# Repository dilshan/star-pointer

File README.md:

# StarPointer - Electronic Finderscope

StarPointer is a virtual electronic finderscope for astronomical telescopes. This device works with [*Stellarium*](http://stellarium.org) and helps the observer identify objects in the sky.

This sensor kit builds around the STM32F103C8 microcontroller, ADXL345 3-axis accelerometer, and HMC5883L 3-axis magnetometer. It communicates with the PC using the inbuilt USB peripheral of the STM32F103C8 microcontroller.

StarPointer is an open-source project. This repository has all the schematics, PCB design files, firmware source codes, and application source codes.

The complete documentation of this project is in the [wiki section](https://github.com/dilshan/star-pointer/wiki) of this repository. The PCB Gerber files and compiled binaries are also available in the [release section](https://github.com/dilshan/star-pointer/releases) of this repository. The PCB of the StarPointer can also [order from the *PCBWay* website](https://www.pcbway.com/project/shareproject/StarPointer_virtual_electronic_finderscope_2c7c17a4.html).

All the content of this project is distributed under the terms of the following license:

-   Hardware License: [CERN-OHL-W 2.0](https://ohwr.org/cern_ohl_w_v2.txt)
-   Software License: [MIT](https://github.com/dilshan/star-pointer/blob/main/LICENSE)
-   [Documentation](https://github.com/dilshan/star-pointer/wiki) License: [CC BY 4.0](https://creativecommons.org/licenses/by/4.0/)

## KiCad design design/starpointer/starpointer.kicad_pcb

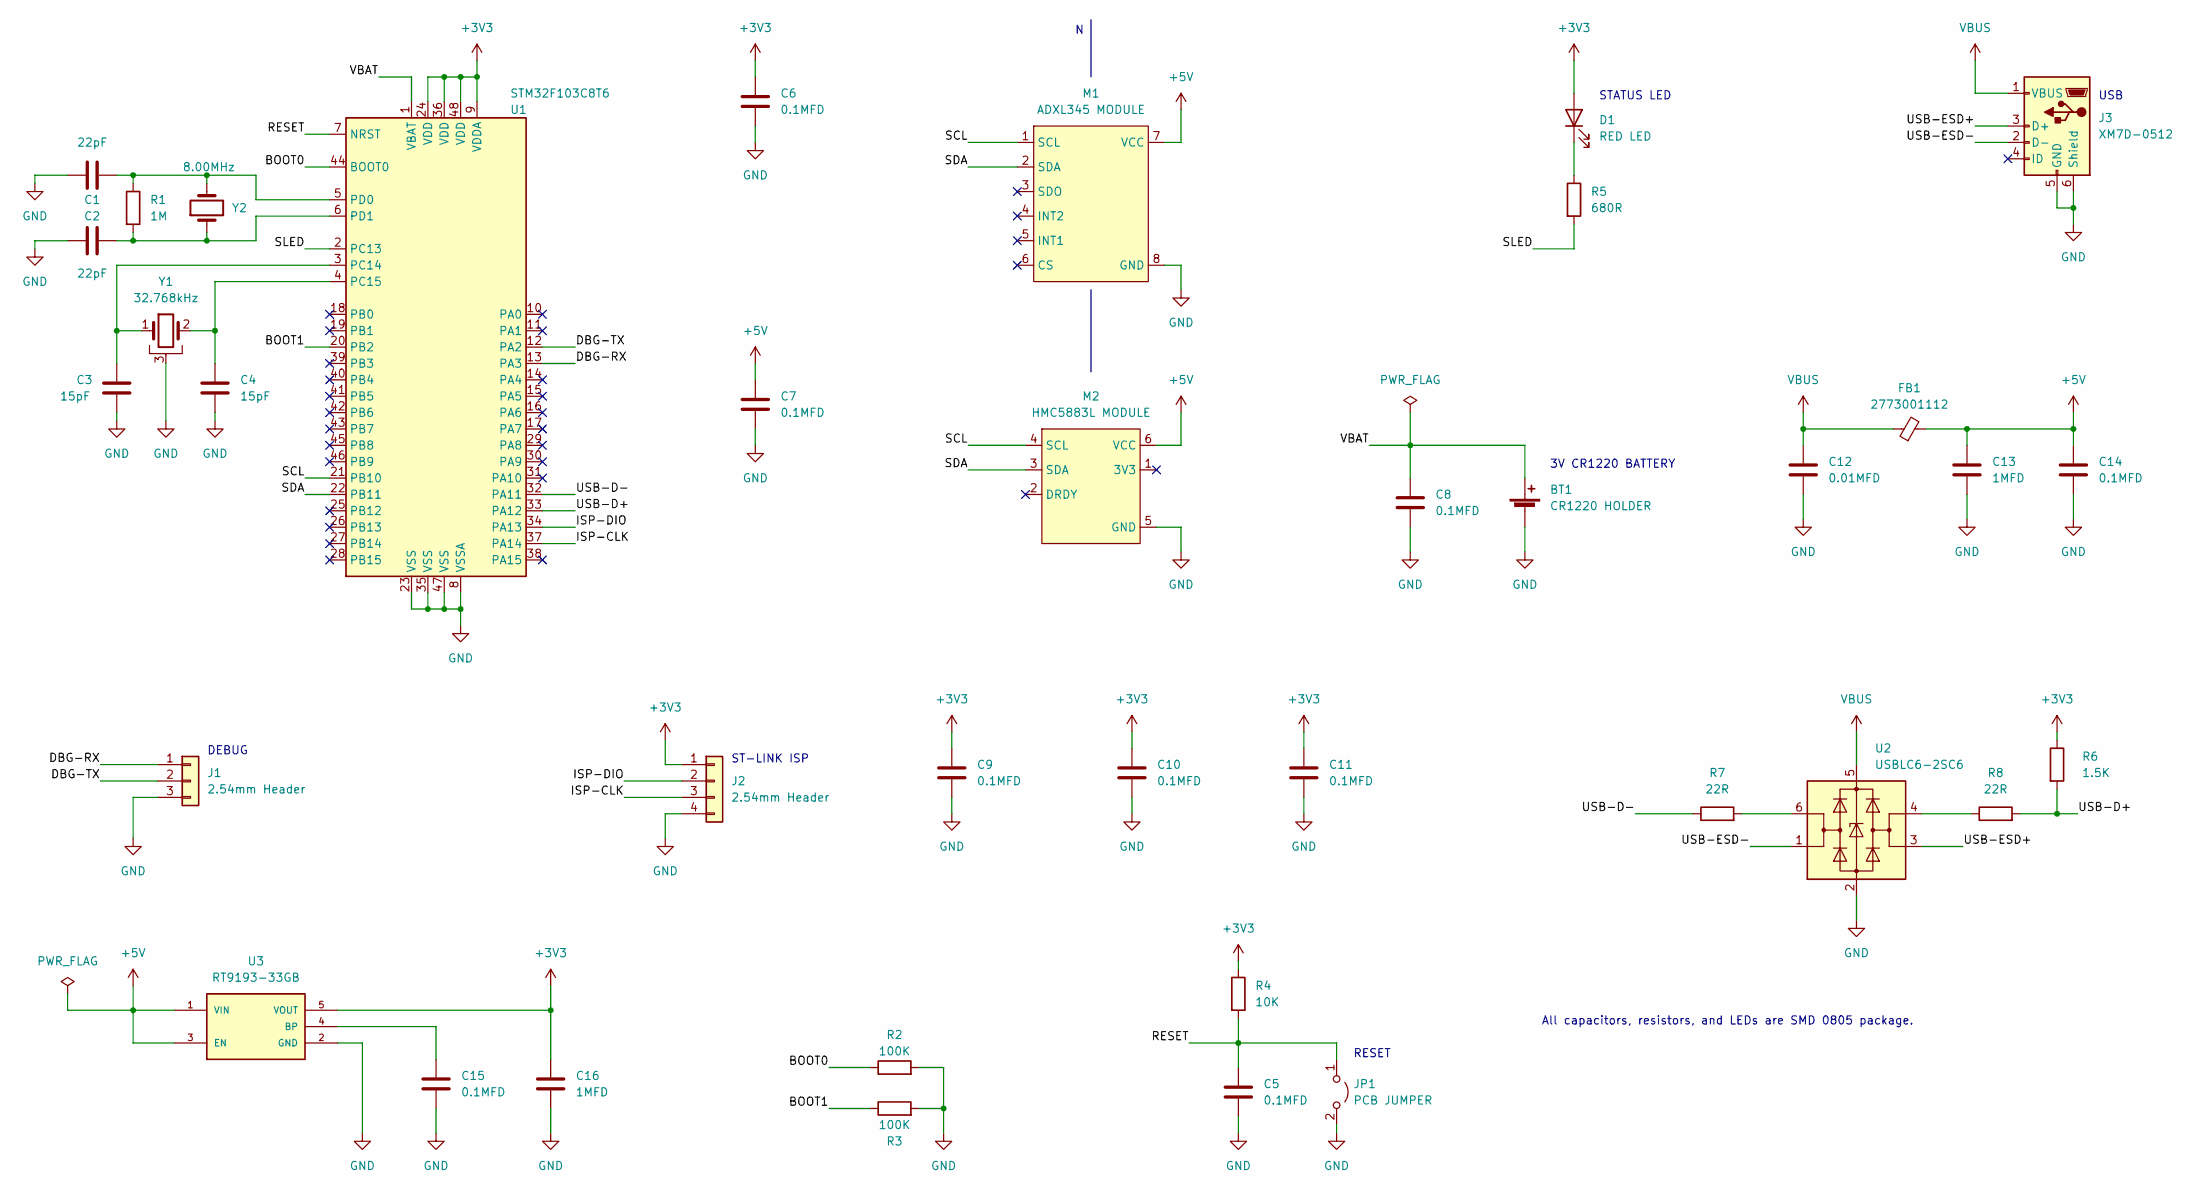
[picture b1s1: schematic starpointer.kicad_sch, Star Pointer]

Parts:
BT1: CR1220 HOLDER; MPD_BC501SM-TR
C1, C2: 22pF; C_0805_2012Metric_Pad1.18x1.45mm_HandSolder
C3, C4: 15pF; C_0805_2012Metric_Pad1.18x1.45mm_HandSolder
C5, C6, C7, C8, C9, C10, C11, C14, C15: 0.1MFD; C_0805_2012Metric_Pad1.18x1.45mm_HandSolder
C12: 0.01MFD; C_0805_2012Metric_Pad1.18x1.45mm_HandSolder
C13, C16: 1MFD; C_0805_2012Metric_Pad1.18x1.45mm_HandSolder
D1: RED LED; LED_0805_2012Metric_Pad1.15x1.40mm_HandSolder
FB1: 2773001112; L_Axial_L5.0mm_D3.6mm_P10.00mm_Horizontal_Murata_BL01RN1A2A2
J1: 2.54mm Header; PinHeader_1x03_P2.54mm_Vertical
J2: 2.54mm Header; PinHeader_1x04_P2.54mm_Vertical
J3: XM7D-0512; OMRON_XM7D-0512
JP1: PCB JUMPER; SolderJumper-2_P1.3mm_Open_Pad1.0x1.5mm
M1: ADXL345 MODULE
M2: HMC5883L MODULE
R1: 1M; R_0805_2012Metric_Pad1.20x1.40mm_HandSolder
R2, R3: 100K; R_0805_2012Metric_Pad1.20x1.40mm_HandSolder
R4: 10K; R_0805_2012Metric_Pad1.20x1.40mm_HandSolder
R5: 680R; R_0805_2012Metric_Pad1.20x1.40mm_HandSolder
R6: 1.5K; R_0805_2012Metric_Pad1.20x1.40mm_HandSolder
R7, R8: 22R; R_0805_2012Metric_Pad1.20x1.40mm_HandSolder
U1: STM32F103C8T6; LQFP-48_7x7mm_P0.5mm
U2: USBLC6-2SC6; SOT-23-6
U3: RT9193-33GB; SOT-23-5_HandSoldering
Y1: 32.768kHz; Crystal_AT310_D3.0mm_L10.0mm_Horizontal_1EP_style1
Y2: 8.00MHz; Crystal_HC49-U_Vertical

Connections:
+3V3: C6.1, C9.1, C10.1, C11.1, C16.1, D1.2 (A), J2.1, R4.1, R6.1, U1.9 (VDDA), U1.24 (VDD), U1.36 (VDD), U1.48 (VDD), U3.5 (VOUT)
+5V: C7.1, C13.1, C14.1, FB1.2, M1.7 (VCC), M2.6 (VCC), U3.1 (VIN), U3.3 (EN)
/BOOT0: R2.1, U1.44 (BOOT0)
/BOOT1: R3.1, U1.20 (PB2)
/DBG-RX: J1.1, U1.13 (PA3)
/DBG-TX: J1.2, U1.12 (PA2)
/ISP-CLK: J2.3, U1.37 (PA14)
/ISP-DIO: J2.2, U1.34 (PA13)
/RESET: C5.1, JP1.1 (A), R4.2, U1.7 (NRST)
/SCL: M1.1 (SCL), M2.4 (SCL), U1.21 (PB10)
/SDA: M1.2 (SDA), M2.3 (SDA), U1.22 (PB11)
/SLED: R5.2, U1.2 (PC13)
/USB-D+: R6.2, R8.2, U1.33 (PA12)
/USB-D-: R7.1, U1.32 (PA11)
/USB-ESD+: J3.3 (D+), U2.3 (I/O2)
/USB-ESD-: J3.2 (D-), U2.1 (I/O1)
/VBAT: BT1.1 (+), C8.1, U1.1 (VBAT)
GND: BT1.2 (-), C1.1, C2.1, C3.2, C4.2, C5.2, C6.2, C7.2, C8.2, C9.2, C10.2, C11.2, C12.2, C13.2, C14.2, C15.2, C16.2, J1.3, J2.4, J3.5 (GND), J3.6 (Shield), JP1.2 (B), M1.8 (GND), M2.5 (GND), R2.2, R3.2, U1.8 (VSSA), U1.23 (VSS), U1.35 (VSS), U1.47 (VSS), U2.2 (GND), U3.2 (GND), Y1.3
unnamed: C1.2, R1.1, U1.5 (PD0), Y2.2
unnamed: C2.2, R1.2, U1.6 (PD1), Y2.1
unnamed: C3.1, U1.3 (PC14), Y1.1
unnamed: C4.1, U1.4 (PC15), Y1.2
unnamed: C15.1, U3.4 (BP)
unnamed: D1.1 (K), R5.1
unnamed: R7.2, U2.6 (I/O1)
unnamed: R8.1, U2.4 (I/O2)
VBUS: C12.1, FB1.1, J3.1 (VBUS), U2.5 (VBUS)

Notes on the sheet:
3V CR1220 BATTERY
DEBUG
STATUS LED
All capacitors, resistors, and LEDs are SMD 0805 package.
ST-LINK ISP
RESET
USB

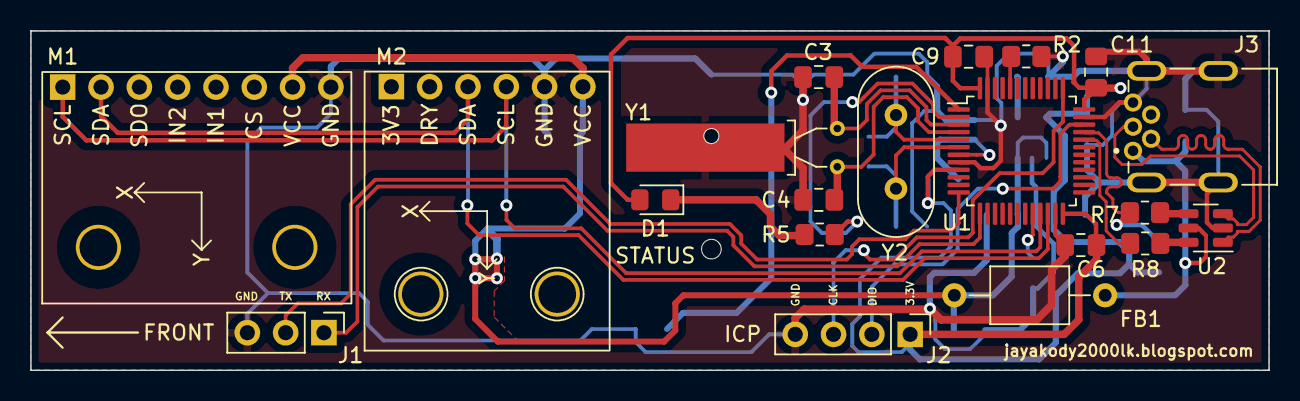
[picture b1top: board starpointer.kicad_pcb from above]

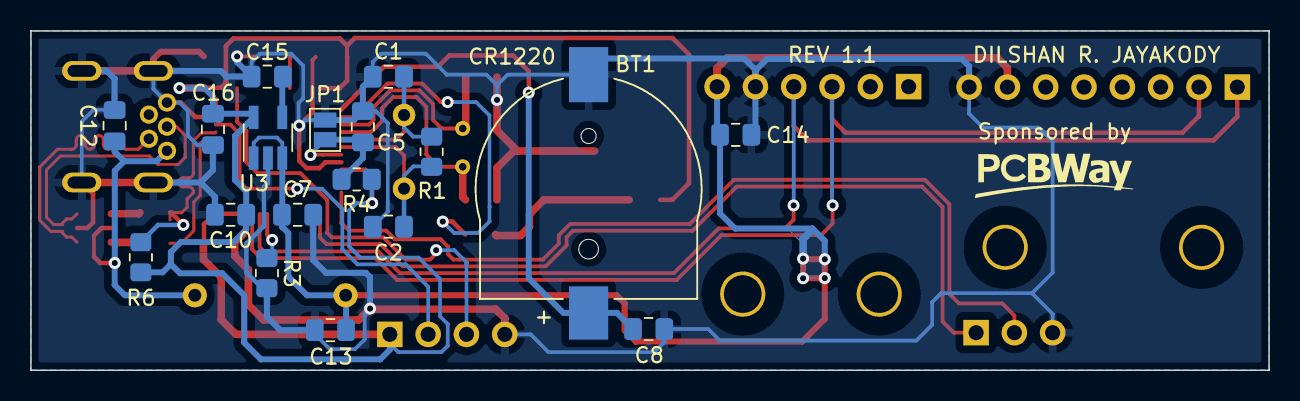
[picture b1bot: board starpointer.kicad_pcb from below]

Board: 2 copper layers, 82.1 x 22.5 mm, 38 parts (18 on the bottom side), 27 nets.

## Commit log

2022-01-15 Initial version of star-pointer with RA and DEC command support.
2022-01-16 Add initial version of Star Pointer Sync tool.
2022-01-17 Add validations on UI elements. Include system time support.
2022-01-17 Add sensor commands to set UTC date/time and location.
2022-01-18 Add sensor configuration update flow with error handling.
2022-01-18 Add application icon. :framed_picture:
2022-01-18 Code refactor by grouping states related text.
2022-01-19 Add directory to store 3rd party components and libraries.
2022-01-19 Set sensor command formats similar to LX200 protocol.
2022-01-20 Provide sync utility support on STM32F103C8 firmware.
2022-01-20 Add customized version of TLazSerial component.
2022-01-20 Fix pitch angle issue with relative to the magnetometer.
2022-01-23 Add battery backup support to RTC. Fix issues in RTC year.
2022-01-23 Modify update routines to send UTC time to the sensor.
2022-01-25 Update configuration manager to store data in BKP registers.
2022-01-25 Optimize load and save routines of the configuration manager.
2022-01-25 Add RA and DEC offset support into the sensor readings.
2022-01-29 Initial version of Star Pointer schematic and PCB.
2022-02-01 Add note about the component types. Add PDF version of the schematic.
2022-02-12 Add status indicator support into the firmware.
2022-06-16 Add MIT license into the project.
2022-06-16 Add license information to the firmware source code.
2022-06-16 Add .gitignore file. Update sync source files with license information.
2022-06-16 Update project settings of the sync tool.
2022-06-16 Fix USB connection issue due to the missing pull-up in USB-D+ line.
2022-06-16 Add PDF version of the StarPointer schematic.
2022-06-17 Add SVG image of the StarPointer PCB.
2022-06-17 :framed_picture: Add StarPointer thumbnail image.
2022-06-17 Add initial version of readme.md file.
2022-06-17 Add thumbnail image and YouTube link to the readme.md file.
2022-06-17 Minor update in readme.md file.
2022-06-17 Add resource directory and ICP pinouts.
2022-06-18 Add image of serial terminal pinouts.
2022-06-18 Add board and enclosure dimensions.
2022-06-18 Add wiki and release links into the readme.md file.
2022-06-18 Add STL file of the StarPointer enclosure.
2022-06-25 Add OSHWA certification mark - LK000012.
2022-06-25 Add OSHWA certification ID - LK000012
2022-06-25 Add PCBWay order address.
